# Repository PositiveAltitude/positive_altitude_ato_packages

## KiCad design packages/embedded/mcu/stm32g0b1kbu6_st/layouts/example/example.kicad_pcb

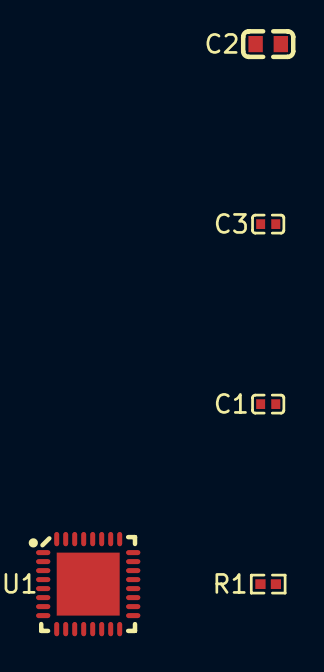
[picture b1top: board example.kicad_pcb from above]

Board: 2 copper layers, 5 parts (0 on the bottom side), 4 nets, no tracks yet.

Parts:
C1, C3: C0402
C2: C0603
R1: R0402
U1: QFN-32_L5.0-W5.0-P0.50-TL-EP3.5

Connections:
PA14_BOOT0: R1.1, U1.25
PF2_NRST: C1.1, U1.6
hv: C2.1, C3.1, U1.4
lv: C1.2, C2.2, C3.2, R1.2, U1.5, U1.33

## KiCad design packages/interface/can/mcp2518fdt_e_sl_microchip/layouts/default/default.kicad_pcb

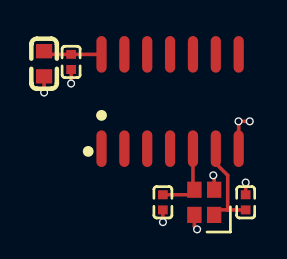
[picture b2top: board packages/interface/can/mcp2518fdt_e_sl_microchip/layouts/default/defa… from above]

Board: 2 copper layers, 6 parts (0 on the bottom side), 4 nets.

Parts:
C1, C2, C4: C0402
C3: C0603
U1: SOIC-14_L8.7-W3.9-P1.27-LS6.0-BL
XTAL1: CRYSTAL-SMD_4P-L2.0-W1.6-BL

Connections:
1: C2.1, U1.5, XTAL1.3
1-1: C1.1, U1.6, XTAL1.1
hv: C3.1, C4.1, U1.14
lv: C1.2, C2.2, C3.2, C4.2, U1.7, XTAL1.2, XTAL1.4

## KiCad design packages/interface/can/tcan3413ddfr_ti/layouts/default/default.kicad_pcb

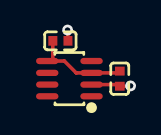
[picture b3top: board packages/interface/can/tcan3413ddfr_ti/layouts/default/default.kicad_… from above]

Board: 2 copper layers, 3 parts (0 on the bottom side), 2 nets.

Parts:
C1, C2: C0402
U1: SOT-23-8_L2.9-W1.6-P0.65-LS2.8-BR

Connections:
hv: C1.1, C2.1, U1.3, U1.5
lv: C1.2, C2.2, U1.2
